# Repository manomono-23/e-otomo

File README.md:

# e-Otomo えおとも

**オープンソースAIフォトフレーム - あなたの写真をe-paperディスプレイに美しく表示**

e-Otomo（えおとも）は、nRF52840を使用したデバイスで、Bluetooth Low Energy (BLE) を使用してスマートフォン等から写真を送信し、e-paperディスプレイに表示するオープンソースプロジェクトです。

## 特徴

- **WebBluetooth対応**: スマートフォンブラウザから直接写真を送信
- **e-paperディスプレイ**: 電子ペーパーで写真を美しく表現
- **複数の描画モード**: Floyd-Steinberg、Atkinson、Ordered、Thresholdディザリング
- **省電力設計**: CR2032電池で長時間動作
- **自動圧縮**: RLE圧縮により効率的なデータ転送

## ハードウェア構成

### 必要な部品

- **マイコン**: Seeed Studio XIAO nRF52840
- **ディスプレイ**:
  - 3色（白・黒・赤）: [Waveshare 1.54inch e-Paper Module B](https://www.waveshare.com/1.54inch-e-Paper-B.htm)
  - 2色（白・黒）: [1.54" 200x200 E-Ink Display Panel #-765](https://buyepaper.com/products/-765)
- **電源**: CR2032電池

### ピン配置

| nRF52840 | 接続先 | 説明 |
|----------|--------|------|
| 3V3      | e-Paper VCC | 電源 |
| GND      | e-Paper GND | グランド |
| D6       | e-Paper DIN (MOSI) | SPI データ |
| D7       | e-Paper CLK (SCK) | SPI クロック |
| D3       | e-Paper BUSY | ビジー信号 |
| D1       | e-Paper CS | チップセレクト |
| D5       | e-Paper DC | データ/コマンド |
| D4       | e-Paper RST | リセット |
| D2       | プッシュボタン | ウェイクアップ（外部プルダウン抵抗付き）|
| D0       | 赤色LED | ステータス表示 |
| LED_BLUE | 青色LED（内蔵） | ディープスリープ表示 |

## リリース・バージョン

### 主要リリース

- **[v1.0.1-booth-new-release](https://github.com/manomono-23/e-otomo/tree/v1.0.1-booth-new-release)**: Booth出品バージョン
- **[v1.0.0-mft2025](https://github.com/manomono-23/e-otomo/tree/v1.0.0-mft2025)**: Maker Faire Tokyo 2025出品バージョン

## ハードウェア設計

### PCB設計

- **設計ファイル**: `hardware/pcb/PhotoFrameMini_v3.*`
- **設計ツール**: KiCad 8.x
- **レイヤー**: 2層基板

### 筐体設計

- **3Dモデル**: `hardware/case/*`
- **寸法**: 51.9 x 51.9 x 10.7mm
- **材質**: PLA推奨
- **透明アクリル**: `hardware/case/Middle_Acrylic_2mm.svg`（ディスプレイカバー用）
- **透明アクリル**: `hardware/case/Panel_Acrylic_1mm.svg`（ケース中間層用）

### 注意点

⚠️ **3Dプリンター製作時の注意**
- 筐体は3Dプリンターで製作するため、個体によって寸法にばらつきがある場合があります
- 部品の嵌合具合を確認し、必要に応じてやすりがけなどで調整してください

## ソフトウェア構成

### ファームウェア (Arduino)

- **開発環境**: Arduino IDE
- **ライブラリ**:
  - GxEPD2 (e-paper display)
  - Adafruit Bluefruit nRF52 libraries
- **機能**:
  - BLE通信
  - e-paperディスプレイ制御
  - RLE圧縮対応

### Webアプリケーション

- **技術**: HTML5, CSS3, JavaScript (WebBluetooth API)
- **リポジトリ**: [e-Otomo Web Interface](https://github.com/manomono-23/e-otomo-web)
- **ライブデモ**: [e-otomo.manomono.net](http://e-otomo.manomono.net/)
- **機能**:
  - 写真選択とプレビュー
  - 複数の描画モード
  - 自動圧縮最適化
  - iOS/Android対応

## 使い方

### 初回セットアップ

1. **電池を挿入**: CR2032電池をデバイスに挿入
2. **長押し起動**: プッシュボタンを1.5秒以上長押し
3. **QRコード確認**: ディスプレイにQRコードとデバイス名が表示されます
4. **Webアプリアクセス**: スマートフォンでQRコードをスキャンしてWebアプリにアクセス

### 単発送信モード - 1枚の写真を送信

1. **Webアプリを開く**: ブラウザで http://e-otomo.manomono.net/ にアクセス
2. **モード選択**: 「今すぐ1枚送信」タブを選択
3. **写真を選択**: 「写真を選択」ボタンをクリックして表示したい写真を選ぶ
4. **描画モード選択**: 4種類の描画モードから好みのスタイルを選択
   - **Floyd-Steinberg**: 高品質なディザリング（デフォルト）
   - **Atkinson**: 柔らかな印象のディザリング
   - **Ordered**: パターン化されたディザリング
   - **Threshold**: シンプルな2値化
5. **色モード選択**: 2色/3色/4色モードから選択
   - **2色**: 白・黒
   - **3色**: 白・黒・赤
6. **プレビュー確認**: 選択した描画モードでリアルタイムプレビューを確認
7. **デバイスに接続**: 「デバイスに接続」ボタンをクリック
8. **デバイス選択**: Bluetoothダイアログで "e-otomo" で始まるデバイスを選択
9. **送信**: 「送信」ボタンをクリックして写真を転送
10. **表示完了**: e-paperディスプレイに写真が表示されます（約15秒）

### プッシュスイッチの動作

- **短押し（1.5秒未満）**: ディスプレイ更新なしでBluetooth接続開始
  - 電力を節約したい場合に使用
  - QRコードは表示されません
- **長押し（1.5秒以上）**: QRコード表示 + Bluetooth接続開始
  - 初回セットアップ時や、新しいデバイスで接続する場合に使用
  - ディスプレイにQRコードとデバイス名が表示されます

### LED ステータス表示

#### 赤色LED（D0）

| 状態 | LEDパターン | 説明 |
|------|------------|------|
| 起動時 | 10ms点灯・100ms消灯 × 5回 | デバイス起動完了 |
| 動作中 | 10ms点灯・2000ms消灯の繰り返し | Bluetooth接続待機・データ処理中 |
| スリープ前 | 10ms点灯・100ms消灯 × 3回 | 省電力モード移行 |

### 省電力モード

デバイスは以下の条件で自動的にディープスリープに入ります：

- **接続なしタイムアウト**: 起動後30秒以内にBluetooth接続がない場合
- **接続後タイムアウト**: Bluetooth接続後90秒間活動がない場合

ディープスリープ状態では：
- 消費電力が約10μAに削減
- プッシュボタンを押すことで起動
- 青色LEDが常時点灯（ディープスリープ表示）

### トラブルシューティング

#### デバイスが見つからない

1. プッシュボタンを押してBluetooth接続を開始
2. デバイスのLEDが点滅していることを確認
3. スマートフォンのBluetooth設定でデバイスが検出されることを確認
4. ブラウザをリロードして再試行

#### 写真が正しく表示されない

1. 描画モードを変更して再送信
2. 写真のコントラストや明るさを調整
3. 色モードがディスプレイタイプと一致しているか確認

#### 転送が途中で止まる

1. スマートフォンとデバイスの距離を近づける（1m以内推奨）
2. 他のBluetooth機器との干渉を避ける
3. デバイスを再起動（電池を抜き差し）

## 技術仕様

### 電力消費
- **動作時**: 約20mA
- **スリープ時**: 約10μA
- **電池寿命**: CR2032で約6ヶ月（1日1回使用想定）

### 通信仕様
- **プロトコル**: Bluetooth Low Energy 4.2+
- **転送速度**: 最大15KB/s（RLE圧縮時）
- **対応OS**: Android, iOS（Bluefy経由）, PC

### ディスプレイ仕様
- **サイズ**: 1.54インチ
- **解像度**: 200×200ピクセル
- **色数**: 3色（白・黒・赤） / 2色（白・黒）

### データ圧縮
- **アルゴリズム**: Run-Length Encoding (RLE)
- **圧縮率**: 平均60-90%（画像内容による）
- **ピクセル値形式**: [length, value]ペア

## 開発への貢献

このプロジェクトはオープンソースです。貢献を歓迎します！

## ライセンス

このプロジェクトは Creative Commons Attribution-NonCommercial-ShareAlike 4.0 International License の下でライセンスされています。

- **非商用利用のみ**: 商用目的での使用は禁止されています
- **表示**: 適切なクレジット表記が必要です
- **継承**: 改変版も同じライセンスで配布する必要があります

詳細は [LICENSE](LICENSE) ファイルまたは https://creativecommons.org/licenses/by-nc-sa/4.0/ を参照してください。

## 謝辞

- [Adafruit](https://www.adafruit.com/) - nRF52ライブラリ
- [Waveshare](https://www.waveshare.com/) - e-paperディスプレイ
- [Seeed Studio](https://www.seeedstudio.com/) - XIAO nRF52840

## 関連リポジトリ

- **メインファームウェア**: [e-Otomo](https://github.com/manomono-23/e-otomo) (このリポジトリ)
- **Webアプリケーション**: [e-Otomo-web](https://github.com/manomono-23/e-otomo-web)
- **画像データ送信ツール**: [e-otomo.manomono.net](http://e-otomo.manomono.net/)

## リンク

- [プロジェクトホームページ](https://kawashimadaichi.tokyo/e-otomo)

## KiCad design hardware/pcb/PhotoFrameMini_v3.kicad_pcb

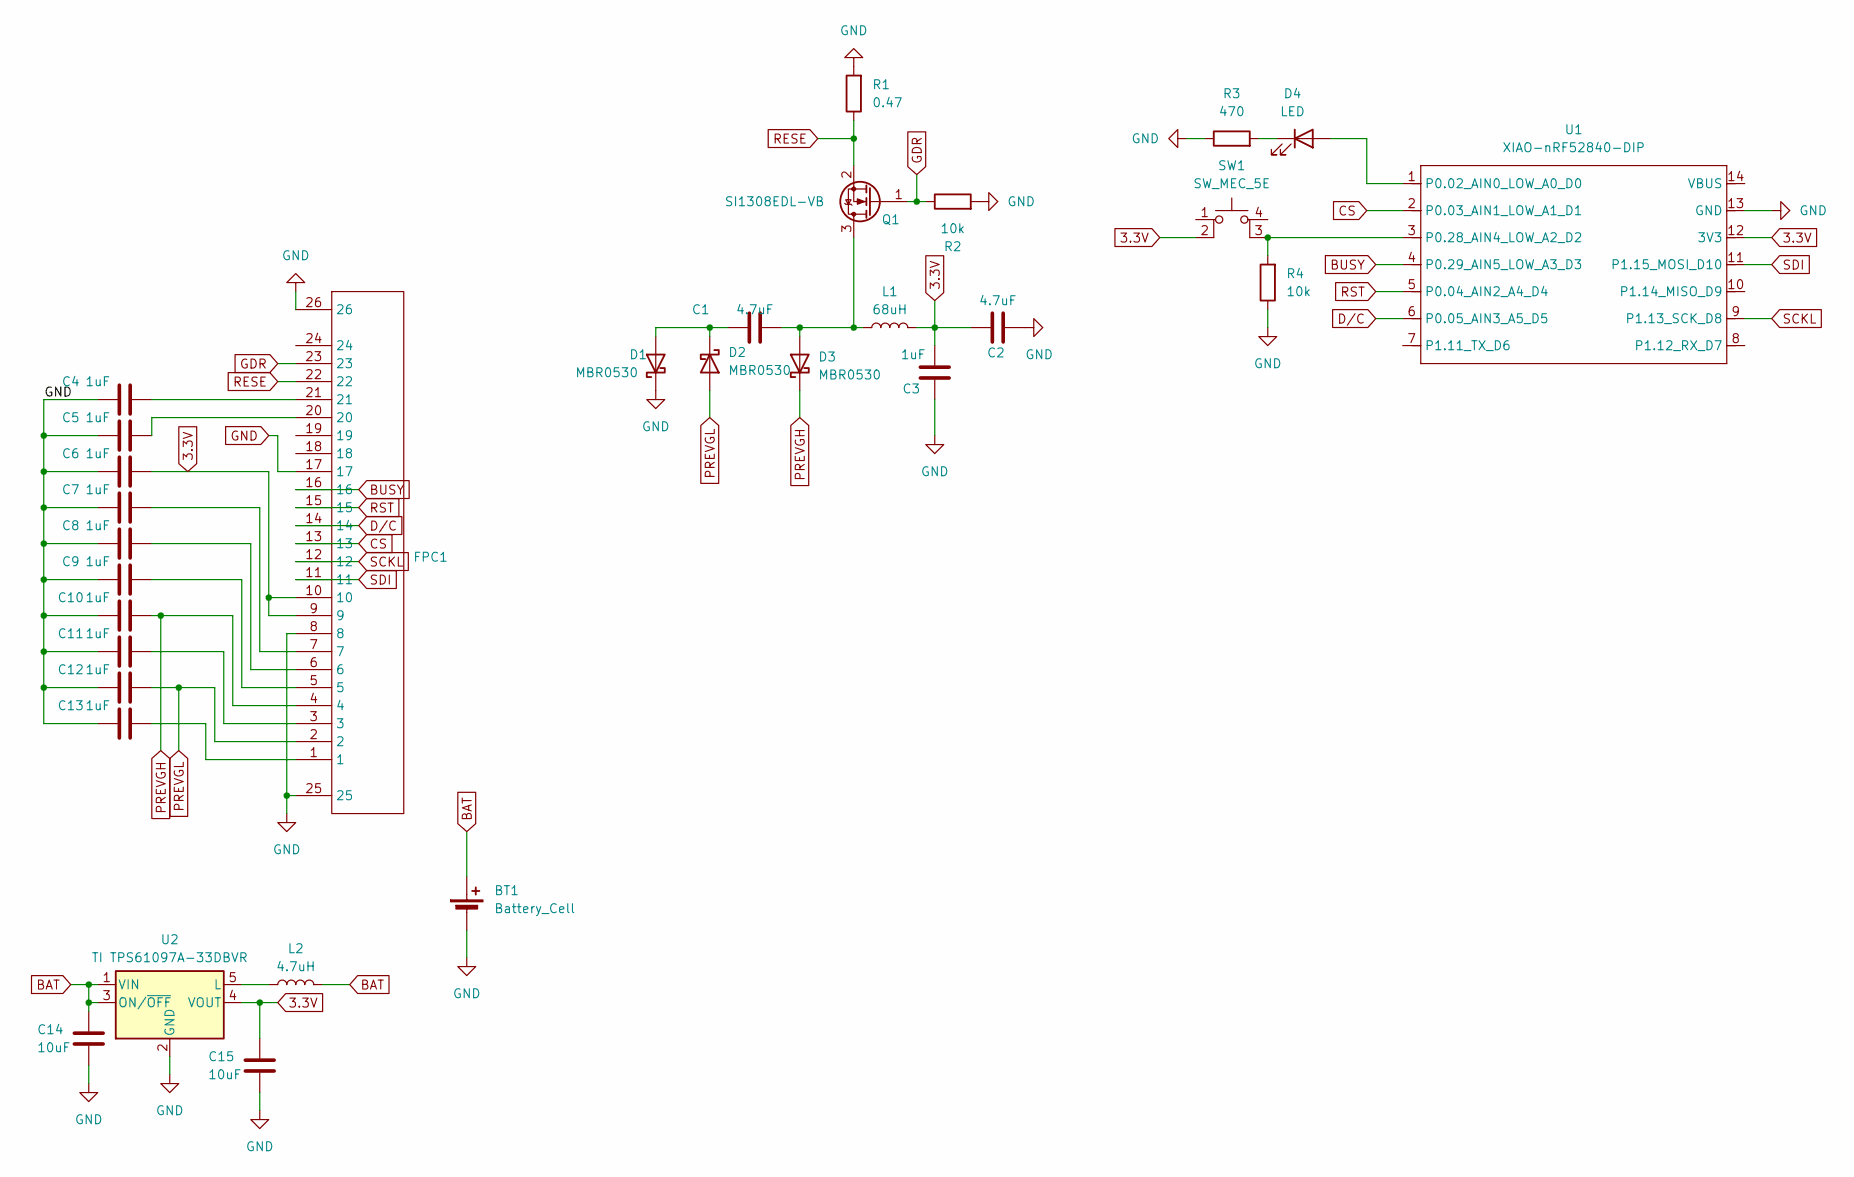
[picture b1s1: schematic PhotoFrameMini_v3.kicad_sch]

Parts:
BT1: Battery_Cell; BAT-SMD_MY-2032-08; LCSC C964831
C1, C2: 4.7uF; C_0603_1608Metric; LCSC C6119856
C3, C6, C7, C8, C9, C10, C11, C12, C13: 1uF; C_0603_1608Metric; LCSC C15849
C4, C5: 1uF; C_0603_1608Metric; LCSC C5673
C14, C15: 10uF; C_0603_1608Metric; LCSC C96446
D1, D2, D3: MBR0530; SOD-123_L2.8-W1.8-LS3.7-RD; LCSC C77336
D4: LED; LED_0603_1608Metric; LCSC C84263
FPC1: FPC-SMD_AFC07-S24ECA-00; Manufacturer Part AFC07-S24ECA-00; LCSC Part Name 间距:0.5mm P数:24P 抽屉式 上接
L1: 68uH; C76843; LCSC C76843
L2: 4.7uH; IND-SMD_L2.5-W2.0-VLS252012CX-150M; LCSC C5832360
Q1: SI1308EDL-VB; SOT-323_SC-70; LCSC C469327
R1: 0.47; R_0603_1608Metric; LCSC C3013349
R2, R4: 10k; R_0603_1608Metric; LCSC C2930027
R3: 470; R_0603_1608Metric; LCSC C2907172
SW1: SW_MEC_5E; SW-SMD_4P-L5.2-W5.2-P3.70-LS6.4; LCSC C49234134
U1: XIAO-nRF52840-DIP
U2: TI TPS61097A-33DBVR; SOT-23-5; LCSC C2071172

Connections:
3.3V: C2.1, C3.2, C6.2, C15.1, FPC1.9, FPC1.10, L1.2, SW1.2, U1.12 (3V3), U2.4 (VOUT)
BAT: BT1.1 (+), C14.1, L2.2, U2.1 (VIN), U2.3 (ON/~OFF)
BUSY: FPC1.16, U1.4 (P0.29_AIN5_LOW_A3_D3)
CS: FPC1.13, U1.2 (P0.03_AIN1_LOW_A1_D1)
D/C: FPC1.14, U1.6 (P0.05_AIN3_A5_D5)
GDR: FPC1.23, Q1.1 (G), R2.1
GND: BT1.2 (-), C2.2, C3.1, C4.1, C5.1, C6.1, C7.1, C8.1, C9.1, C10.1, C11.1, C12.1, C13.1, C14.2, C15.2, D1.1 (K), FPC1.8, FPC1.17, FPC1.25, FPC1.26, R1.2, R2.2, R3.1, R4.1, U1.13 (GND), U2.2 (GND)
unnamed: C4.2, FPC1.21
unnamed: C5.2, FPC1.20
unnamed: C7.2, FPC1.7
unnamed: C8.2, FPC1.6
unnamed: C9.2, FPC1.5
unnamed: C11.2, FPC1.3
unnamed: C13.2, FPC1.1
unnamed: C1.1, D1.2 (A), D2.1 (K)
unnamed: C1.2, D3.2 (A), L1.1, Q1.3 (D)
unnamed: D4.2 (A), U1.1 (P0.02_AIN0_LOW_A0_D0)
unnamed: D4.1 (K), R3.2
unnamed: R4.2, SW1.3 (K), U1.3 (P0.28_AIN4_LOW_A2_D2)
unnamed: L2.1, U2.5 (L)
PREVGH: C10.2, D3.1 (K), FPC1.4
PREVGL: C12.2, D2.2 (A), FPC1.2
RESE: FPC1.22, Q1.2 (S), R1.1
RST: FPC1.15, U1.5 (P0.04_AIN2_A4_D4)
SCKL: FPC1.12, U1.9 (P1.13_SCK_D8)
SDI: FPC1.11, U1.11 (P1.15_MOSI_D10)

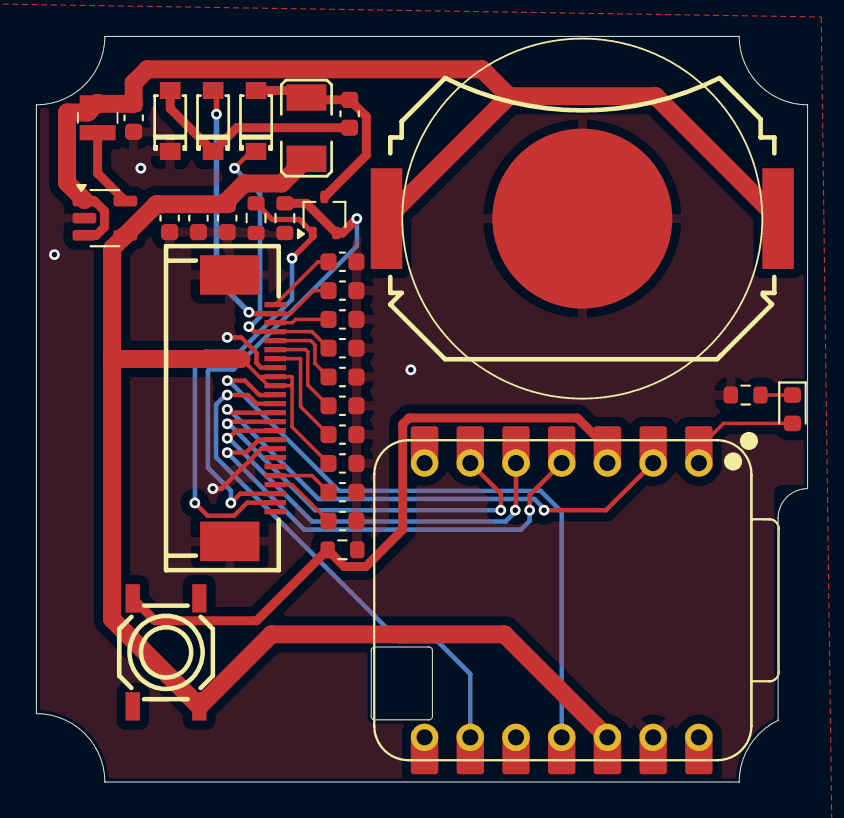
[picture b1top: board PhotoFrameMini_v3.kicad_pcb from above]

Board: 2 copper layers, 42.8 x 41.4 mm, 31 parts (0 on the bottom side), 26 nets.

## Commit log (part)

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2025-09-29 3Dデータupdate
2025-10-04 fixed
2025-10-07 update kicad
2025-10-23 4色電子ペーパー対応
2025-10-24 FICRをデバイス名に含める
2025-11-18 update for 4c
